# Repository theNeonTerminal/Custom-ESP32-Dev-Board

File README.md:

# Custom ESP32 Dev Board

This is my 1st time building a custom ESP32 dev board. This board here features the ESP-WROOM-32D chip and CP2102 USB to TTL for programming the chip. 

---

## Hardware Design

### 01 / Circuit Schematic

<div align="center">

</div>

### 02 / PCB Layout

<div align="center">

</div>

### 03 / PCB 3D View

<div align="center">

</div>
---

## Features:
- Runs on a USB Type C port
- Main Chipset: ESP-WROOM-32D and CP2102 USB to TTL
- Extra Features added to board: 12 WS2812B RGB LEDs, 4 push buttons and a rotary encoder.
- Designed in KiCAD

This is my 1st time with SMD on PCBs, so the component placement / rotuting isnt of the highest quality. But Ill try my best in future attempts, to improve and make my board better and more unique

--- 

## BoM (Bill of Materials)

| PART | QUANTITY | PACKAGE |
| ---- | -------- | ------- |
| ESP-WROOM-32D | 1 | SMD,25.5x18mm |
| Push Button | 4 | 6mm x 6mm THT |
| Push Button | 2 | SMD,25.5x18mm |
| AMS1117 3V3 | 1 | SOT-223 |
| USBLC6-2SC6-FS | 1 | SOT-23-6L |
| SS8050 | 2 | SOT-23 |
| TF Card H1.8 | 1 | SMD |
| USB Type C Port (Female) | 1 | SMD |
| RED LED | 1 | SMD 0603 |
| WS2812B | 12 | SMD5050-4P |
| 1uF cap | _ | SMD 0603 |
| 22uf cap | 1 | SMD 0603 |
| 4.7uf cap | _ | SMD 0603 |
| 10uf cap | _ | SMD 0603 |
| 22.1K resistor | 1 | SMD 0603 |
| 47.5k resistor | 1 | SMD 0603 |
| 10k resistor | _ | SMD 0603 |
| 5.1k resistor | _ | SMD 0603 |
| 470 resistor | _ | SMd 0603 |

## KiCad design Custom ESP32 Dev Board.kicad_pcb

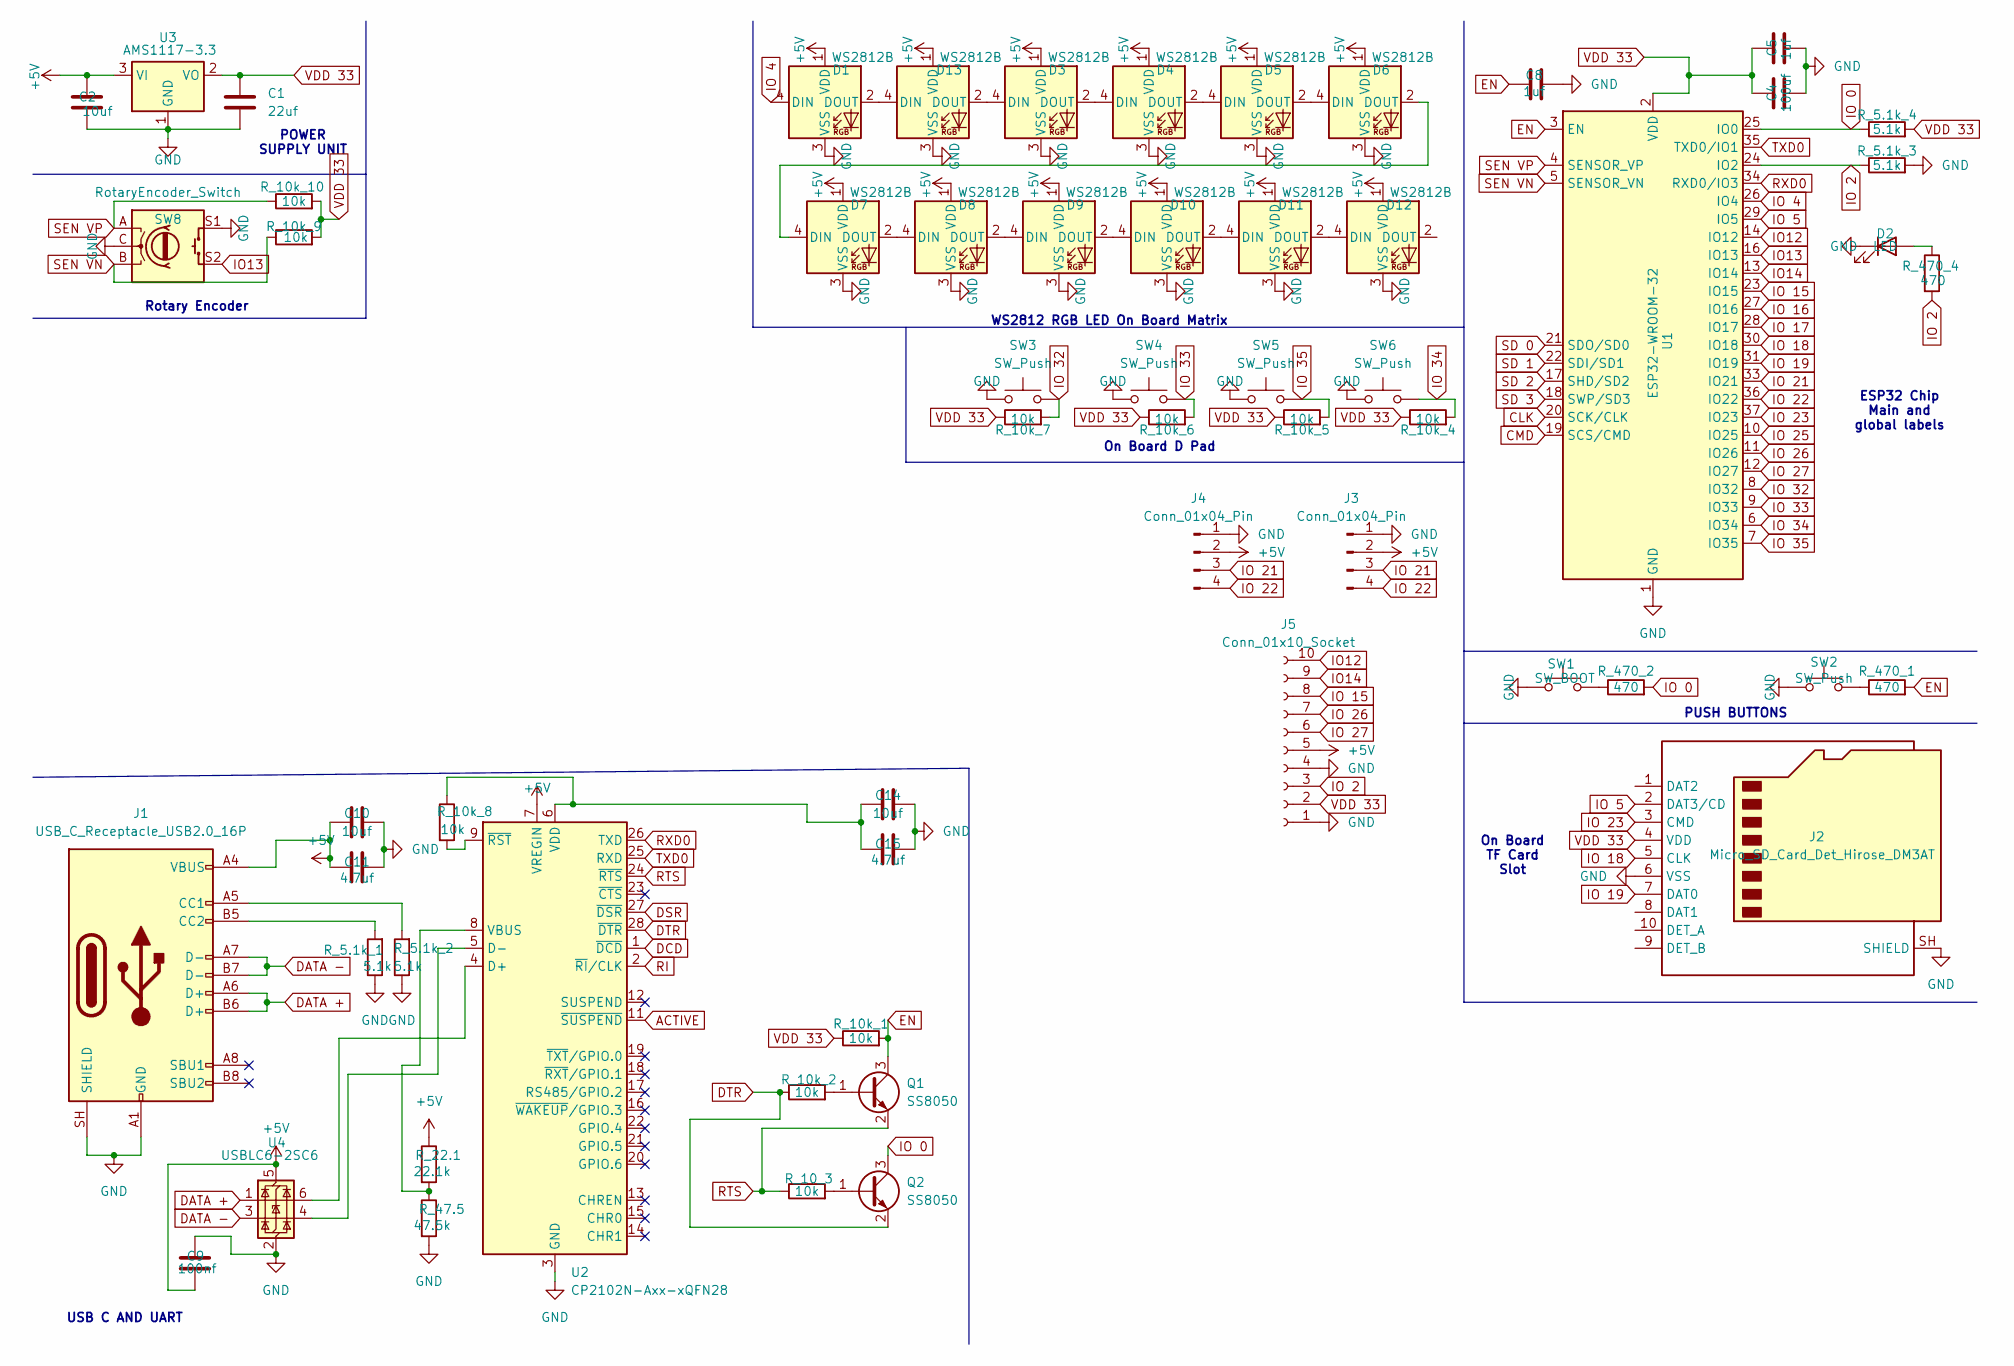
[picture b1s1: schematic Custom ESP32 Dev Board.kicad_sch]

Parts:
C1: 22uf; C_0603_1608Metric
C2, C10, C14: 10uf; C_0603_1608Metric
C4: 100uf; C_0603_1608Metric
C5, C8: 1uf; C_0603_1608Metric
C9: 100nf; C_0603_1608Metric
C11, C15: 4.7uf; C_0603_1608Metric
D1, D3, D4, D5, D6, D7, D8, D9, D10, D11, D12, D13: WS2812B; LED_WS2812B_PLCC4_5.0x5.0mm_P3.2mm
D2: LED; LED_0603_1608Metric
J1: USB_C_Receptacle_USB2.0_16P; USB_C_Receptacle_GCT_USB4105-xx-A_16P_TopMnt_Horizontal
J2: Micro_SD_Card_Det_Hirose_DM3AT; microSD_HC_Hirose_DM3AT-SF-PEJM5
J3, J4: Conn_01x04_Pin; PinSocket_1x04_P2.54mm_Vertical
J5: Conn_01x10_Socket; PinSocket_1x10_P2.54mm_Vertical
Q1, Q2: SS8050; SOT-23
R_5.1k_1, R_5.1k_2, R_5.1k_3, R_5.1k_4: 5.1k; R_1206_3216Metric_Pad1.30x1.75mm_HandSolder
R_10_3, R_10k_1, R_10k_2, R_10k_4, R_10k_5, R_10k_6, R_10k_7, R_10k_8, R_10k_9, R_10k_10: 10k; R_0603_1608Metric_Pad0.98x0.95mm_HandSolder
R_22.1: 22.1k; R_0603_1608Metric_Pad0.98x0.95mm_HandSolder
R_47.5: 47.5k; R_01005_0402Metric
R_470_1, R_470_2, R_470_4: 470; R_0603_1608Metric_Pad0.98x0.95mm_HandSolder
SW1: SW_BOOT; SW_Tactile_SPST_NO_Straight_CK_PTS636Sx25SMTRLFS
SW2: SW_Push; SW_Tactile_SPST_NO_Straight_CK_PTS636Sx25SMTRLFS
SW3, SW4, SW5, SW6: SW_Push; SW_PUSH_6mm
SW8: RotaryEncoder_Switch; RotaryEncoder_Alps_EC11E-Switch_Vertical_H20mm
U1: ESP32-WROOM-32
U2: CP2102N-Axx-xQFN28; QFN-28-1EP_5x5mm_P0.5mm_EP3.35x3.35mm
U3: AMS1117-3.3; SOT-223-3_TabPin2
U4: USBLC6-2SC6; SOT-23-6

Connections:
+5V: C2.1, C9.2, C10.1, C11.1, D1.1 (VDD), D3.1 (VDD), D4.1 (VDD), D5.1 (VDD), D6.1 (VDD), D7.1 (VDD), D8.1 (VDD), D9.1 (VDD), D10.1 (VDD), D11.1 (VDD), D12.1 (VDD), D13.1 (VDD), J1.A4 (VBUS), J1.A9 (VBUS), J1.B4 (VBUS), J1.B9 (VBUS), J3.2, J4.2, J5.5, R_22.1.1, U2.7 (VREGIN), U3.3 (VI), U4.5 (VBUS)
ACTIVE: U2.11 (~SUSPEND)
CLK: U1.20 (SCK/CLK)
CMD: U1.19 (SCS/CMD)
DATA +: J1.A6 (D+), J1.B6 (D+), U4.1 (I/O1)
DATA -: J1.A7 (D-), J1.B7 (D-), U4.3 (I/O2)
DCD: U2.1 (~DCD)
DSR: U2.27 (~DSR)
DTR: Q2.2 (E), R_10k_2.1, U2.28 (~DTR)
EN: C8.1, Q1.3 (C), R_10k_1.2, R_470_1.2, U1.3 (EN)
GND: C1.2, C2.2, C4.2, C5.2, C8.2, C9.1, C10.2, C11.2, C14.2, C15.2, D1.3 (VSS), D2.1 (K), D3.3 (VSS), D4.3 (VSS), D5.3 (VSS), D6.3 (VSS), D7.3 (VSS), D8.3 (VSS), D9.3 (VSS), D10.3 (VSS), D11.3 (VSS), D12.3 (VSS), D13.3 (VSS), J1.A1 (GND), J1.A12 (GND), J1.B1 (GND), J1.B12 (GND), J1.SH (SHIELD), J2.6 (VSS), J2.SH (SHIELD), J3.1, J4.1, J5.1, J5.4, R_5.1k_1.1, R_5.1k_2.1, R_5.1k_3.2, R_47.5.2, SW1.1, SW2.1, SW3.1, SW4.1, SW5.1, SW6.1, SW8.C, SW8.S1, U1.1 (GND), U1.15 (GND), U1.38 (GND), U1.39 (GND), U2.3 (GND), U2.29 (GND), U3.1 (GND), U4.2 (GND)
IO12: J5.10, U1.14 (IO12)
IO13: SW8.S2, U1.16 (IO13)
IO14: J5.9, U1.13 (IO14)
IO 0: Q2.3 (C), R_5.1k_4.1, R_470_2.2, U1.25 (IO0)
IO 2: J5.3, R_5.1k_3.1, R_470_4.2, U1.24 (IO2)
IO 4: D1.4 (DIN), U1.26 (IO4)
IO 5: J2.2 (DAT3/CD), U1.29 (IO5)
IO 15: J5.8, U1.23 (IO15)
IO 16: U1.27 (IO16)
IO 17: U1.28 (IO17)
IO 18: J2.5 (CLK), U1.30 (IO18)
IO 19: J2.7 (DAT0), U1.31 (IO19)
IO 21: J3.3, J4.3, U1.33 (IO21)
IO 22: J3.4, J4.4, U1.36 (IO22)
IO 23: J2.3 (CMD), U1.37 (IO23)
IO 25: U1.10 (IO25)
IO 26: J5.7, U1.11 (IO26)
IO 27: J5.6, U1.12 (IO27)
IO 32: R_10k_7.2, SW3.2, U1.8 (IO32)
IO 33: R_10k_6.2, SW4.2, U1.9 (IO33)
IO 34: R_10k_4.2, SW6.2, U1.6 (IO34)
IO 35: R_10k_5.2, SW5.2, U1.7 (IO35)
unnamed: D1.2 (DOUT), D13.4 (DIN)
unnamed: D2.2 (A), R_470_4.1
unnamed: D3.2 (DOUT), D4.4 (DIN)
unnamed: D4.2 (DOUT), D5.4 (DIN)
unnamed: D5.2 (DOUT), D6.4 (DIN)
unnamed: D6.2 (DOUT), D7.4 (DIN)
unnamed: D7.2 (DOUT), D8.4 (DIN)
unnamed: D8.2 (DOUT), D9.4 (DIN)
unnamed: D9.2 (DOUT), D10.4 (DIN)
unnamed: D10.2 (DOUT), D11.4 (DIN)
unnamed: D11.2 (DOUT), D12.4 (DIN)
unnamed: D3.4 (DIN), D13.2 (DOUT)
unnamed: J1.A5 (CC1), R_5.1k_2.2
unnamed: J1.B5 (CC2), R_5.1k_1.2
unnamed: Q1.1 (B), R_10k_2.2
unnamed: Q2.1 (B), R_10_3.2
unnamed: R_470_1.1, SW2.2
unnamed: R_470_2.1, SW1.2
unnamed: U2.4 (D+), U4.6 (I/O1)
unnamed: U2.5 (D-), U4.4 (I/O2)
unnamed: R_22.1.2, R_47.5.1, U2.8 (VBUS)
unnamed: C14.1, C15.1, R_10k_8.1, U2.6 (VDD)
unnamed: R_10k_8.2, U2.9 (~RST)
RI: U2.2 (~RI/CLK)
RTS: Q1.2 (E), R_10_3.1, U2.24 (~RTS)
RXD0: U1.34 (RXD0/IO3), U2.26 (TXD)
SD 0: U1.21 (SDO/SD0)
SD 1: U1.22 (SDI/SD1)
SD 2: U1.17 (SHD/SD2)
SD 3: U1.18 (SWP/SD3)
SEN VN: R_10k_9.1, SW8.B, U1.5 (SENSOR_VN)
SEN VP: R_10k_10.1, SW8.A, U1.4 (SENSOR_VP)
TXD0: U1.35 (TXD0/IO1), U2.25 (RXD)
VDD 33: C1.1, C4.1, C5.1, J2.4 (VDD), J5.2, R_5.1k_4.2, R_10k_1.1, R_10k_4.1, R_10k_5.1, R_10k_6.1, R_10k_7.1, R_10k_9.2, R_10k_10.2, U1.2 (VDD), U3.2 (VO)

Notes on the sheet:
On Board D Pad
Rotary Encoder
PUSH BUTTONS
On Board TF Card Slot
USB C AND UART
WS2812 RGB LED On Board Matrix
POWER SUPPLY UNIT
ESP32 Chip Main and global labels

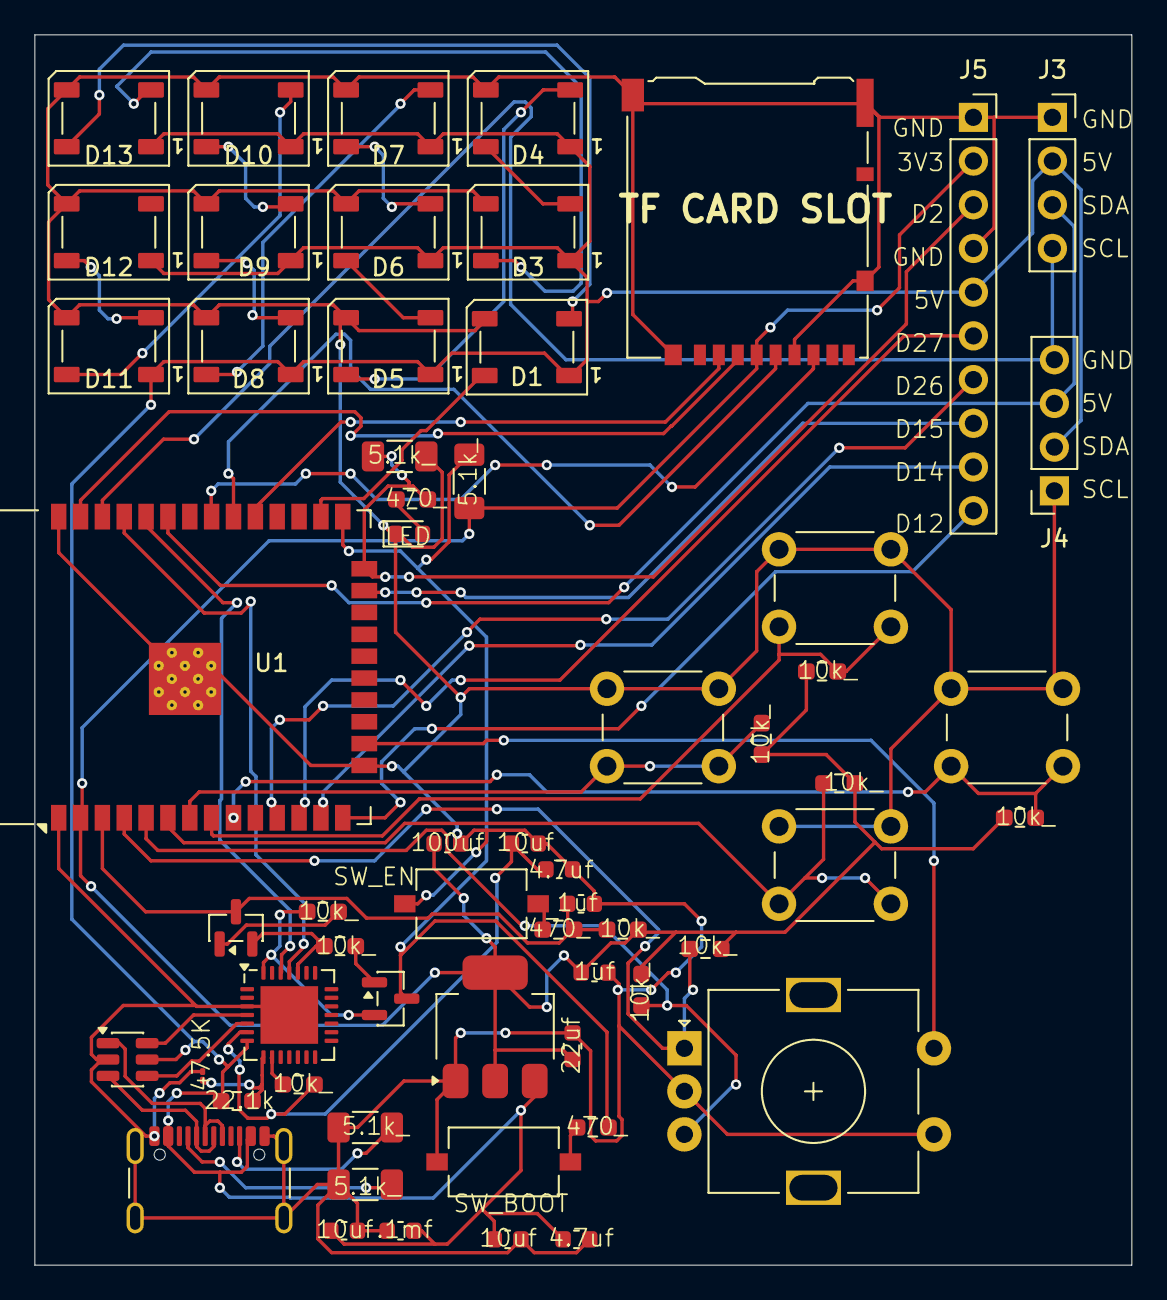
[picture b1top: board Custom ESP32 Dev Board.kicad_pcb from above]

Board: 2 copper layers, 63.8 x 71.5 mm, 60 parts (0 on the bottom side), 54 nets.
